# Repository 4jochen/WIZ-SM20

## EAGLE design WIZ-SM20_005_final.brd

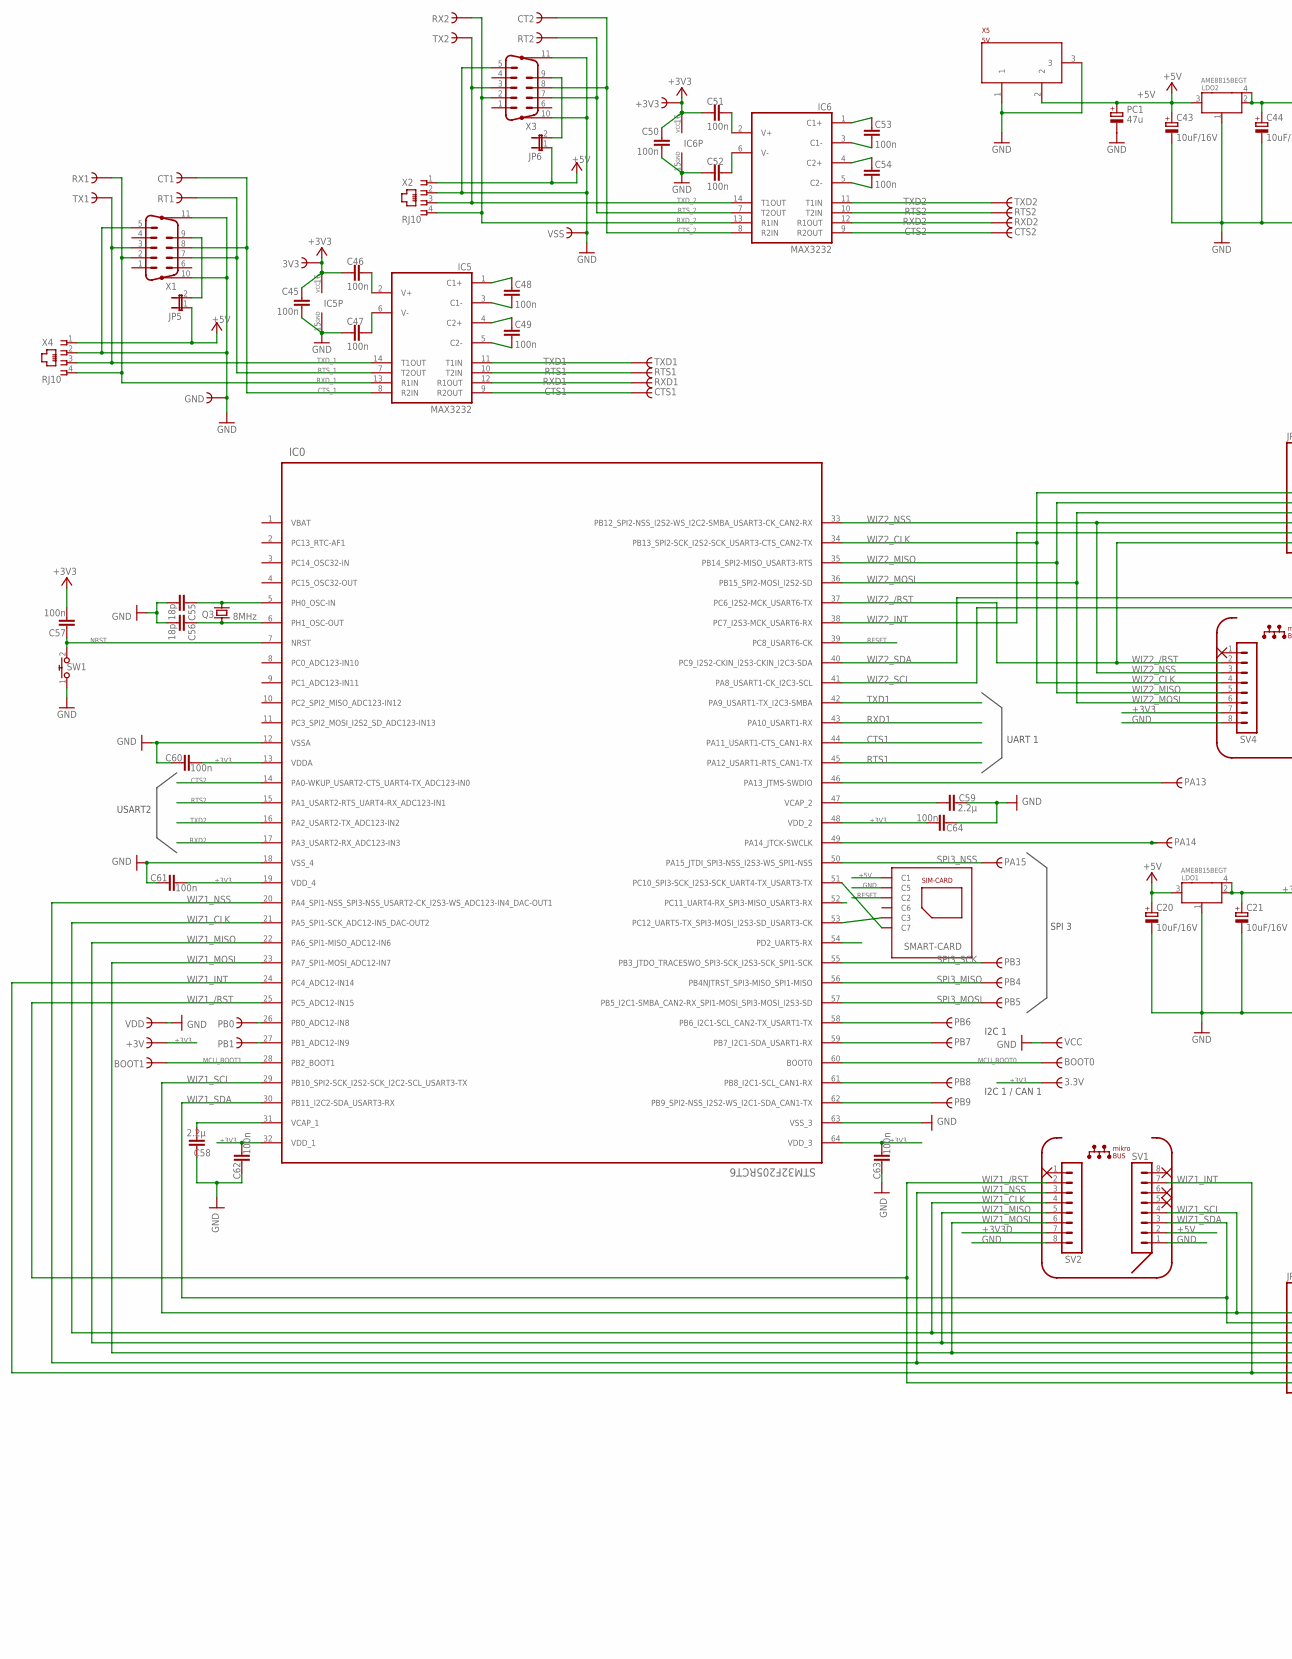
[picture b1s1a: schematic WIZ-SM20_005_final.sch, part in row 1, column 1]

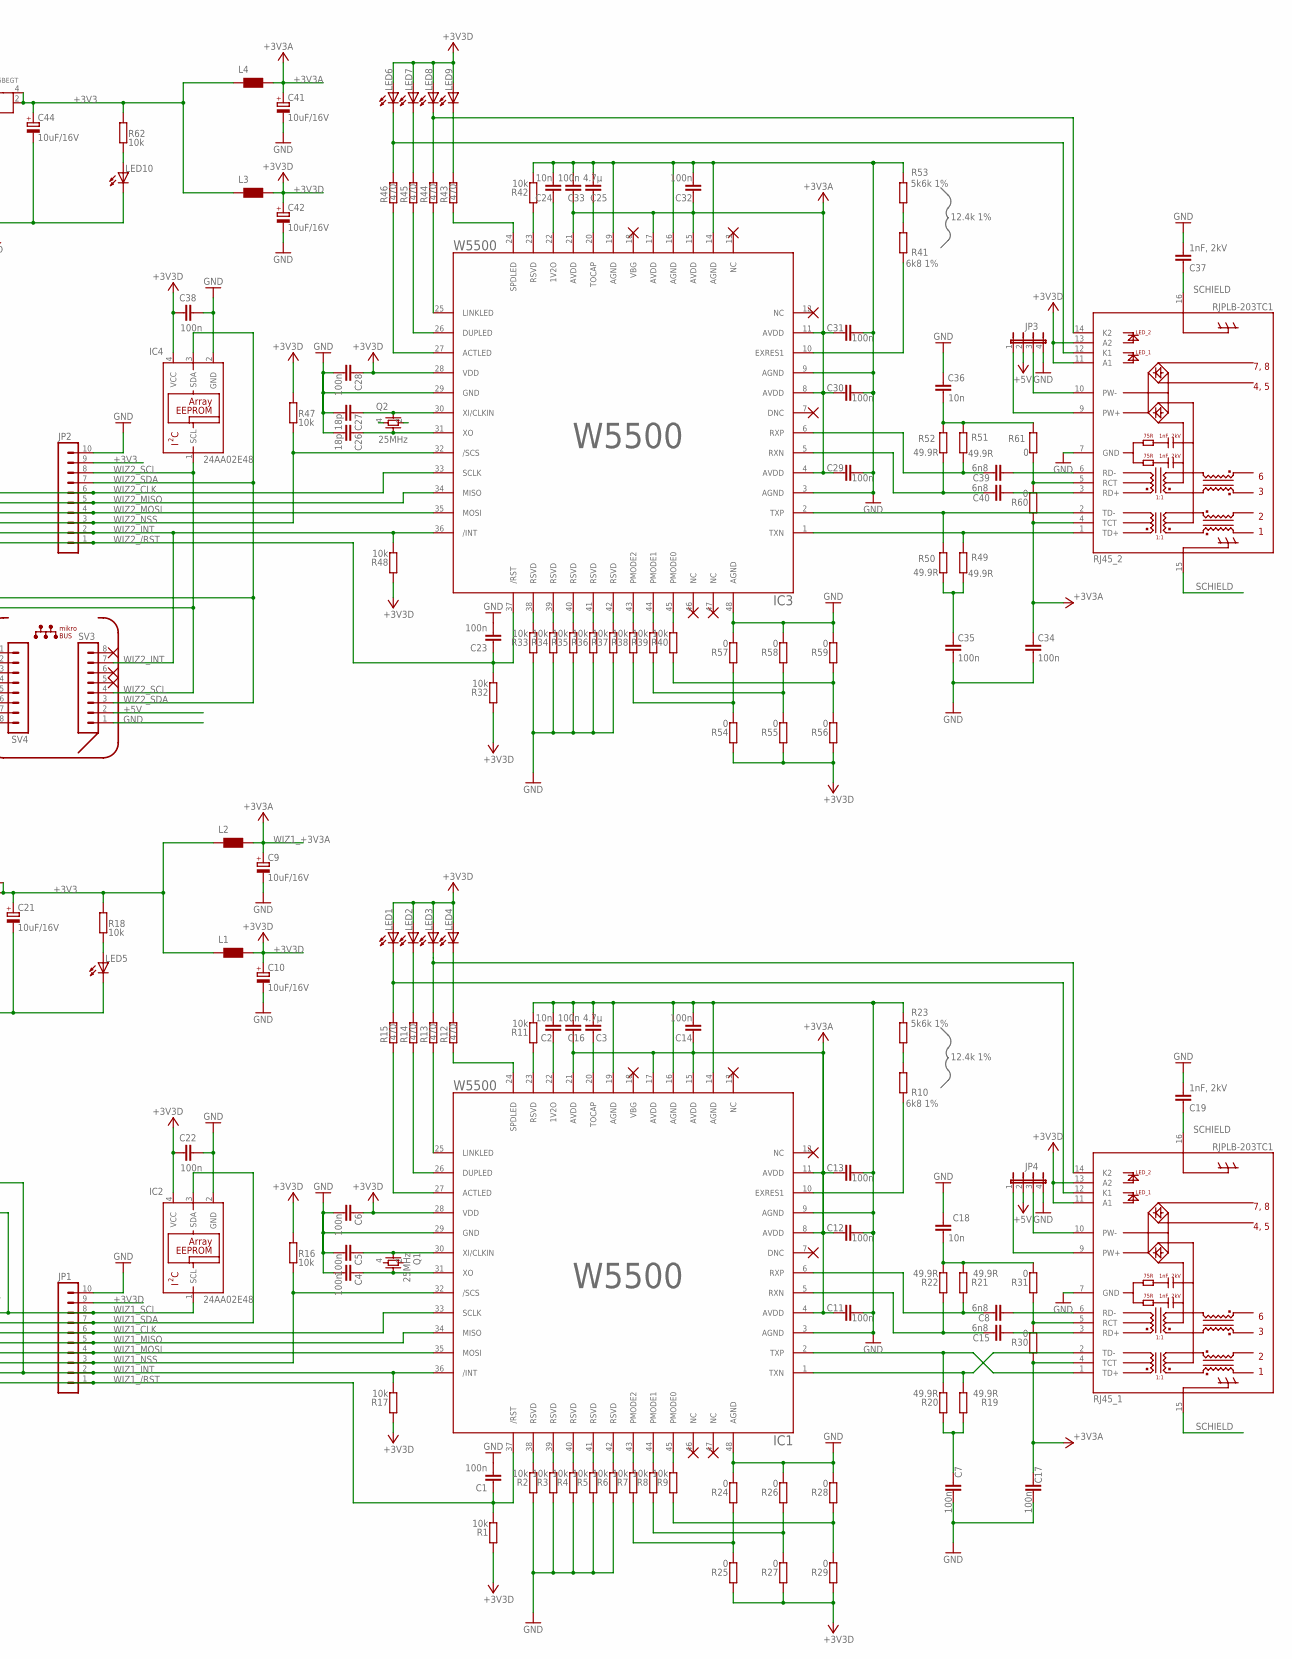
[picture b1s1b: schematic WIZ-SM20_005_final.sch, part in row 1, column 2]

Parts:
3.3V, 3V3: HALFHOLE
+3V, +3V3: HALFHOLE
BOOT0, BOOT1: HALFHOLE
C1, C23: 100n; C0603K
C2, C18, C24, C36: 10n; C0402K
C3, C25: 4.7µ; C0603K
C4, C5, C6, C7, C11, C12, C13, C14, C16, C17, C22, C28, C29, C30, C31, C32, C33, C34, C35, C38, C45, C46, C47, C48, C49, C50, C51, C52, C53, C54, C57, C60, C61, C62, C63, C64: 100n; C0402K
C8, C15, C39, C40: 6n8; C0402K
C9, C10, C20, C21, C41, C42, C43, C44: 10uF/16V; A/3216-18R
C19, C37: 1nF, 2kV; C3216
C26, C27, C55, C56: 18p; C0402K
C58, C59: 2.2µ; C0603K
CT1, CT2: HALFHOLE
CTS1, CTS2: HALFHOLE
GND: HALFHOLE
IC0: STM32F205RCT6; QFP50P1200X1200X160-64N
IC1, IC3: W5500; LQFP48
IC2, IC4: 24AA02E48; SOT23-5L
IC5, IC6: MAX3232; TSSOP16-L
JP1, JP2: @ Tessel; MA10-1
JP3, JP4: JP4E; JP4
JP5, JP6: JP1E; JP1
L1, L2, L3, L4: WE-CBF_0603; 0603
LDO1, LDO2: AME8815BEGT; SOT223
LED1, LED2, LED3, LED4, LED5, LED6, LED7, LED8, LED9, LED10: LEDCHIPLED_0603; CHIPLED_0603
PA13, PA14, PA15: HALFHOLE
PB0, PB1, PB3, PB4, PB5, PB6, PB7, PB8, PB9: HALFHOLE
PC1: 47u; A/3216-18R
Q1, Q2: 25MHz; SMD02502-4
Q3: 8MHz; ABM7
R1, R2, R3, R4, R5, R6, R7, R8, R9, R11, R16, R17, R18, R32, R33, R34, R35, R36, R37, R38, R39, R40, R42, R47, R48, R62: 10k; R0402
R10, R41: 6k8 1%; R0402
R12, R13, R14, R15, R43, R44, R45, R46: 470; R0402
R19, R20, R21, R22, R49, R50, R51, R52: 49.9R; R0402
R23, R53: 5k6k 1%; R0402
R24, R25, R26, R27, R28, R29, R30, R31, R54, R55, R56, R57, R58, R59, R60, R61: 0; R0402
RJ45_1, RJ45_2: RJPLB-203TC1; RJPLB-203
RT1, RT2: HALFHOLE
RTS1, RTS2: HALFHOLE
RX1, RX2: HALFHOLE
RXD1, RXD2: HALFHOLE
SMART-CARD: 7111S2015X02LF
SV1, SV2, SV3, SV4: MA08-1
SW1: Reset; 1302
TX1, TX2: HALFHOLE
TXD1, TXD2: HALFHOLE
VCC: HALFHOLE
VDD: HALFHOLE
VSS: HALFHOLE
X1, X3: M09HPSLIM_SMD; NORCOMP_SMD
X2, X4: RJ10; 520249-2
X5: 5V; POWERSUPPLY_DC-21MM

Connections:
+3V3: 3.3V.P$1, 3V3.P$1, +3V.P$1, +3V3.P$1, C21.+, C44.+, C45.2, C46.1, C50.2, C51.1, C60.2, C61.2, C62.2, C63.2, C64.2, IC0.13 (VDDA), IC0.19 (VDD_4), IC0.32 (VDD_1), IC0.48 (VDD_2), IC0.64 (VDD_3), IC5.16 (VCC), IC6.16 (VCC), JP2.9, L1.2, L2.2, L3.2, L4.2, LDO1.2, LDO1.4, LDO2.2, LDO2.4, R18.2, R62.2, SV4.7
+3V3A: C29.1, C30.1, C31.1, C32.1, C33.1, C34.1, C41.+, IC3.4 (AVDD), IC3.8 (AVDD), IC3.11 (AVDD), IC3.15 (AVDD), IC3.17 (AVDD), IC3.21 (AVDD), L4.1, R60.2, RJ45_2.4 (TCT)
+3V3D: C6.1, C10.+, C22.1, C28.1, C38.1, C42.+, IC1.28 (VDD), IC2.4 (VCC), IC3.28 (VDD), IC4.4 (VCC), JP1.9, L1.1, L3.1, LED1.A, LED2.A, LED3.A, LED4.A, LED6.A, LED7.A, LED8.A, LED9.A, R1.2, R16.2, R17.2, R25.2, R27.2, R29.2, R32.2, R47.2, R48.2, R54.2, R55.2, R56.2, RJ45_1.11 (A1), RJ45_1.13 (A2), RJ45_2.11 (A1), RJ45_2.13 (A2), SV2.7
+5V: C20.+, C43.+, JP3.2, JP4.2, JP5.1, JP6.1, LDO1.3, LDO2.3, PC1.+, SMART-CARD.C1, SV1.2, SV3.2, X2.1, X4.1, X5.2
ACTLED: IC1.27 (ACTLED), R15.1
ACTLED1: IC3.27 (ACTLED), R46.1
CTS1: CTS1.P$1, IC0.44 (PA11_USART1-CTS_CAN1-RX), IC5.9 (R2OUT)
CTS2: CTS2.P$1, IC0.14 (PA0-WKUP_USART2-CTS_UART4-TX_ADC123-IN0), IC6.9 (R2OUT)
CTS_1: CT1.P$1, IC5.8 (R2IN), X1.8
CTS_2: CT2.P$1, IC6.8 (R2IN), X3.8
GND: C1.2, C2.2, C3.2, C4.2, C5.2, C6.2, C7.2, C9.-, C10.-, C11.2, C12.2, C13.2, C14.2, C16.2, C17.2, C18.2, C19.2, C20.-, C21.-, C22.2, C23.2, C24.2, C25.2, C26.2, C27.2, C28.2, C29.2, C30.2, C31.2, C32.2, C33.2, C34.2, C35.2, C36.2, C37.2, C38.2, C41.-, C42.-, C43.-, C44.-, C45.1, C47.1, C50.1, C52.1, C55.2, C56.2, C58.1, C59.1, C60.1, C61.1, C62.1, C63.1, C64.1, GND.P$1, IC0.12 (VSSA), IC0.18 (VSS_4), IC0.63 (VSS_3), IC1.3 (AGND), IC1.9 (AGND), IC1.14 (AGND), IC1.16 (AGND), IC1.19 (AGND), IC1.29 (GND), IC1.48 (AGND), IC2.2 (GND), IC3.3 (AGND), IC3.9 (AGND), IC3.14 (AGND), IC3.16 (AGND), IC3.19 (AGND), IC3.29 (GND), IC3.48 (AGND), IC4.2 (GND), IC5.15 (GND), IC6.15 (GND), JP1.10, JP2.10, JP3.4, JP4.4, LDO1.1, LDO2.1, LED5.C, LED10.C, PC1.-, Q2.2 (PD1), Q2.4 (PD2), R2.2, R3.2, R4.2, R5.2, R6.2, R11.1, R23.1, R24.1, R26.1, R28.1, R33.2, R34.2, R35.2, R36.2, R37.2, R42.1, R53.1, R57.1, R58.1, R59.1, RJ45_1.7 (GND), RJ45_2.7 (GND), SMART-CARD.C5, SV1.1, SV2.8, SV3.1, SV4.8, SW1.1, VCC.P$1, VDD.P$1, VSS.P$1, X1.5, X1.10 (G1), X1.11 (G2), X2.2, X3.5, X3.10 (G1), X3.11 (G2), X4.2, X5.1, X5.3
MCU_BOOT0: BOOT0.P$1, IC0.60 (BOOT0)
MCU_BOOT1: BOOT1.P$1, IC0.28 (PB2_BOOT1)
unnamed: C8.1, RJ45_1.6 (RD-)
unnamed: C15.1, RJ45_1.3 (RD+)
unnamed: IC3.38 (RSVD), R33.1
unnamed: IC1.25 (LINKLED), R13.1
unnamed: R10.1, R23.2
unnamed: IC3.39 (RSVD), R34.1
unnamed: IC3.40 (RSVD), R35.1
unnamed: IC3.41 (RSVD), R36.1
unnamed: IC1.23 (RSVD), R11.2
unnamed: IC1.38 (RSVD), R2.1
unnamed: IC1.39 (RSVD), R3.1
unnamed: IC1.40 (RSVD), R4.1
unnamed: IC1.41 (RSVD), R5.1
unnamed: IC1.42 (RSVD), R6.1
unnamed: IC1.43 (PMODE2), R7.1
unnamed: IC1.44 (PMODE1), R8.1
unnamed: IC1.45 (PMODE0), R9.1
unnamed: R9.2, R28.2, R29.1
unnamed: R8.2, R26.2, R27.1
unnamed: R7.2, R24.2, R25.1
unnamed: IC3.42 (RSVD), R37.1
unnamed: IC1.10 (EXRES1), R10.2
unnamed: C2.1, IC1.22 (1V2O)
unnamed: C3.1, IC1.20 (TOCAP)
unnamed: IC1.24 (SPDLED), R12.1
unnamed: IC1.26 (DUPLED), R14.1
unnamed: IC3.43 (PMODE2), R38.1
unnamed: LED4.C, R12.2
unnamed: LED1.C, R15.2, RJ45_1.12 (K1)
unnamed: LED2.C, R14.2
unnamed: LED3.C, R13.2, RJ45_1.14 (K2)
unnamed: C4.1, IC1.31 (XO), Q1.3 (2)
unnamed: C5.1, IC1.30 (XI/CLKIN), Q1.1
unnamed: LED5.A, R18.1
unnamed: C7.1, R19.2, R20.2
unnamed: C18.1, R21.1, R22.1, R31.1
unnamed: IC3.44 (PMODE1), R39.1
unnamed: IC3.45 (PMODE0), R40.1
unnamed: IC3.10 (EXRES1), R41.2
unnamed: IC3.23 (RSVD), R42.2
unnamed: C24.1, IC3.22 (1V2O)
unnamed: C25.1, IC3.20 (TOCAP)
unnamed: IC3.24 (SPDLED), R43.1
unnamed: IC3.26 (DUPLED), R45.1
unnamed: LED9.C, R43.2
unnamed: LED6.C, R46.2, RJ45_2.12 (K1)
unnamed: LED7.C, R45.2
unnamed: LED8.C, R44.2, RJ45_2.14 (K2)
unnamed: C26.1, IC3.31 (XO), Q2.3 (2)
unnamed: C27.1, IC3.30 (XI/CLKIN), Q2.1
unnamed: C35.1, R49.2, R50.2
unnamed: C36.1, R51.1, R52.1, R61.1
unnamed: IC3.25 (LINKLED), R44.1
unnamed: R41.1, R53.2
unnamed: R38.2, R54.1, R57.2
unnamed: R39.2, R55.1, R58.2
unnamed: R40.2, R56.1, R59.2
unnamed: IC0.46 (PA13_JTMS-SWDIO), PA13.P$1
unnamed: IC0.49 (PA14_JTCK-SWCLK), PA14.P$1
unnamed: LED10.A, R62.1
unnamed: IC0.51 (PC10_SPI3-SCK_I2S3-SCK_UART4-TX_USART3-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), SMART-CARD.C7
unnamed: C55.1, IC0.5 (PH0_OSC-IN), Q3.1
unnamed: C56.1, IC0.6 (PH1_OSC-OUT), Q3.2
unnamed: IC0.26 (PB0_ADC12-IN8), PB0.P$1
unnamed: IC0.27 (PB1_ADC12-IN9), PB1.P$1
unnamed: IC0.53 (PC12_UART5-TX_SPI3-MOSI_I2S3-SD_USART3-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), SMART-CARD.C3
unnamed: IC0.61 (PB8_I2C1-SCL_CAN1-RX), PB8.P$1
unnamed: IC0.62 (PB9_SPI2-NSS_I2S2-WS_I2C1-SDA_CAN1-TX), PB9.P$1
unnamed: IC0.58 (PB6_I2C1-SCL_CAN2-TX_USART1-TX), PB6.P$1
unnamed: C53.2, IC6.1 (C1+)
unnamed: C48.2, IC5.1 (C1+)
unnamed: C48.1, IC5.3 (C1-)
unnamed: C49.2, IC5.4 (C2+)
unnamed: C49.1, IC5.5 (C2-)
unnamed: C46.2, IC5.2 (V+)
unnamed: C47.2, IC5.6 (V-)
unnamed: C53.1, IC6.3 (C1-)
unnamed: C54.2, IC6.4 (C2+)
unnamed: C54.1, IC6.5 (C2-)
unnamed: C51.2, IC6.2 (V+)
unnamed: JP5.2, X1.9
unnamed: C52.2, IC6.6 (V-)
unnamed: IC0.59 (PB7_I2C1-SDA_USART1-RX), PB7.P$1
unnamed: JP6.2, X3.9
unnamed: C58.2, IC0.31 (VCAP_1)
unnamed: C59.2, IC0.47 (VCAP_2)
NRST: C57.1, IC0.7 (NRST), SW1.2
POE+: JP4.1, RJ45_1.9 (PW+)
POE+1: JP3.1, RJ45_2.9 (PW+)
POE-: JP4.3, RJ45_1.10 (PW-)
POE-1: JP3.3, RJ45_2.10 (PW-)
RCT: R30.1, R31.2, RJ45_1.5 (RCT)
RCT1: R60.1, R61.2, RJ45_2.5 (RCT)
RESET: IC0.39 (PC8_USART6-CK), SMART-CARD.C2
RTS1: IC0.45 (PA12_USART1-RTS_CAN1-TX), IC5.10 (T2IN), RTS1.P$1
RTS2: IC0.15 (PA1_USART2-RTS_UART4-RX_ADC123-IN1), IC6.10 (T2IN), RTS2.P$1
RTS_1: IC5.7 (T2OUT), RT1.P$1, X1.7
RTS_2: IC6.7 (T2OUT), RT2.P$1, X3.7
RX2_N: C39.1, RJ45_2.6 (RD-)
RX2_P: C40.1, RJ45_2.3 (RD+)
RXD1: IC0.43 (PA10_USART1-RX), IC5.12 (R1OUT), RXD1.P$1
RXD2: IC0.17 (PA3_USART2-RX_ADC123-IN3), IC6.12 (R1OUT), RXD2.P$1
RXD_1: IC5.13 (R1IN), RX1.P$1, X1.2, X4.4
RXD_2: IC6.13 (R1IN), RX2.P$1, X2.4, X3.2
RXN: C8.2, IC1.6 (RXP), R21.2
RXN1: C39.2, IC3.6 (RXP), R51.2
RXP: C15.2, IC1.5 (RXN), R22.2
RXP1: C40.2, IC3.5 (RXN), R52.2
SCHIELD: C19.1, C37.1, RJ45_1.15 (SCHIELD_1), RJ45_1.16 (SCHIELD_2), RJ45_2.15 (SCHIELD_1), RJ45_2.16 (SCHIELD_2)
SPI3_MISO: IC0.56 (PB4NJTRST_SPI3-MISO_SPI1-MISO), PB4.P$1
SPI3_MOSI: IC0.57 (PB5_I2C1-SMBA_CAN2-RX_SPI1-MOSI_SPI3-MO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), PB5.P$1
SPI3_NSS: IC0.50 (PA15_JTDI_SPI3-NSS_I2S3-WS_SPI1-NSS), PA15.P$1
SPI3_SCK: IC0.55 (PB3_JTDO_TRACESWO_SPI3-SCK_I2S3-SCK_SPI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), PB3.P$1
TX2_N: IC3.2 (TXP), R50.1, RJ45_2.2 (TD-)
TX2_P: IC3.1 (TXN), R49.1, RJ45_2.1 (TD+)
TXD1: IC0.42 (PA9_USART1-TX_I2C3-SMBA), IC5.11 (T1IN), TXD1.P$1
TXD2: IC0.16 (PA2_USART2-TX_ADC123-IN2), IC6.11 (T1IN), TXD2.P$1
TXD_1: IC5.14 (T1OUT), TX1.P$1, X1.3, X4.3
TXD_2: IC6.14 (T1OUT), TX2.P$1, X2.3, X3.3
TXN: IC1.2 (TXP), R20.1, RJ45_1.1 (TD+)
TXP: IC1.1 (TXN), R19.1, RJ45_1.2 (TD-)
VBAT: IC0.1 (VBAT)
VCC: C57.2
WIZ1_+3V3A: C9.+, C11.1, C12.1, C13.1, C14.1, C16.1, C17.1, IC1.4 (AVDD), IC1.8 (AVDD), IC1.11 (AVDD), IC1.15 (AVDD), IC1.17 (AVDD), IC1.21 (AVDD), L2.1, R30.2, RJ45_1.4 (TCT)
WIZ1_/RST: C1.1, IC0.25 (PC5_ADC12-IN15), IC1.37 (/RST), JP1.1, R1.1, SV2.2
WIZ1_CLK: IC0.21 (PA5_SPI1-SCK_ADC12-IN5_DAC-OUT2), IC1.33 (SCLK), JP1.6, SV2.4
WIZ1_INT: IC0.24 (PC4_ADC12-IN14), IC1.36 (/INT), JP1.2, R17.1, SV1.7
WIZ1_MISO: IC0.22 (PA6_SPI1-MISO_ADC12-IN6), IC1.34 (MISO), JP1.5, SV2.5
WIZ1_MOSI: IC0.23 (PA7_SPI1-MOSI_ADC12-IN7), IC1.35 (MOSI), JP1.4, SV2.6
WIZ1_NSS: IC0.20 (PA4_SPI1-NSS_SPI3-NSS_USART2-CK_I2S3-WS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), IC1.32 (/SCS), JP1.3, R16.1, SV2.3
WIZ1_SCL: IC0.29 (PB10_SPI2-SCK_I2S2-SCK_I2C2-SCL_USART3-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), IC2.1 (SCL), JP1.8, SV1.4
WIZ1_SDA: IC0.30 (PB11_I2C2-SDA_USART3-RX), IC2.3 (SDA), JP1.7, SV1.3
WIZ2_/RST: C23.1, IC0.37 (PC6_I2S2-MCK_USART6-TX), IC3.37 (/RST), JP2.1, R32.1, SV4.2
WIZ2_CLK: IC0.34 (PB13_SPI2-SCK_I2S2-SCK_USART3-CTS_CAN2-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), IC3.33 (SCLK), JP2.6, SV4.4
WIZ2_INT: IC0.38 (PC7_I2S3-MCK_USART6-RX), IC3.36 (/INT), JP2.2, R48.1, SV3.7
WIZ2_MISO: IC0.35 (PB14_SPI2-MISO_USART3-RTS), IC3.34 (MISO), JP2.5, SV4.5
WIZ2_MOSI: IC0.36 (PB15_SPI2-MOSI_I2S2-SD), IC3.35 (MOSI), JP2.4, SV4.6
WIZ2_NSS: IC0.33 (PB12_SPI2-NSS_I2S2-WS_I2C2-SMBA_USART3-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), IC3.32 (/SCS), JP2.3, R47.1, SV4.3
WIZ2_SCL: IC0.41 (PA8_USART1-CK_I2C3-SCL), IC4.1 (SCL), JP2.8, SV3.4
WIZ2_SDA: IC0.40 (PC9_I2S2-CKIN_I2S3-CKIN_I2C3-SDA), IC4.3 (SDA), JP2.7, SV3.3

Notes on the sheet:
W5500
12.4k 1%
mikro BUS
USART2
I2C 1 / CAN 1
I2C 1
UART 1
SPI 3

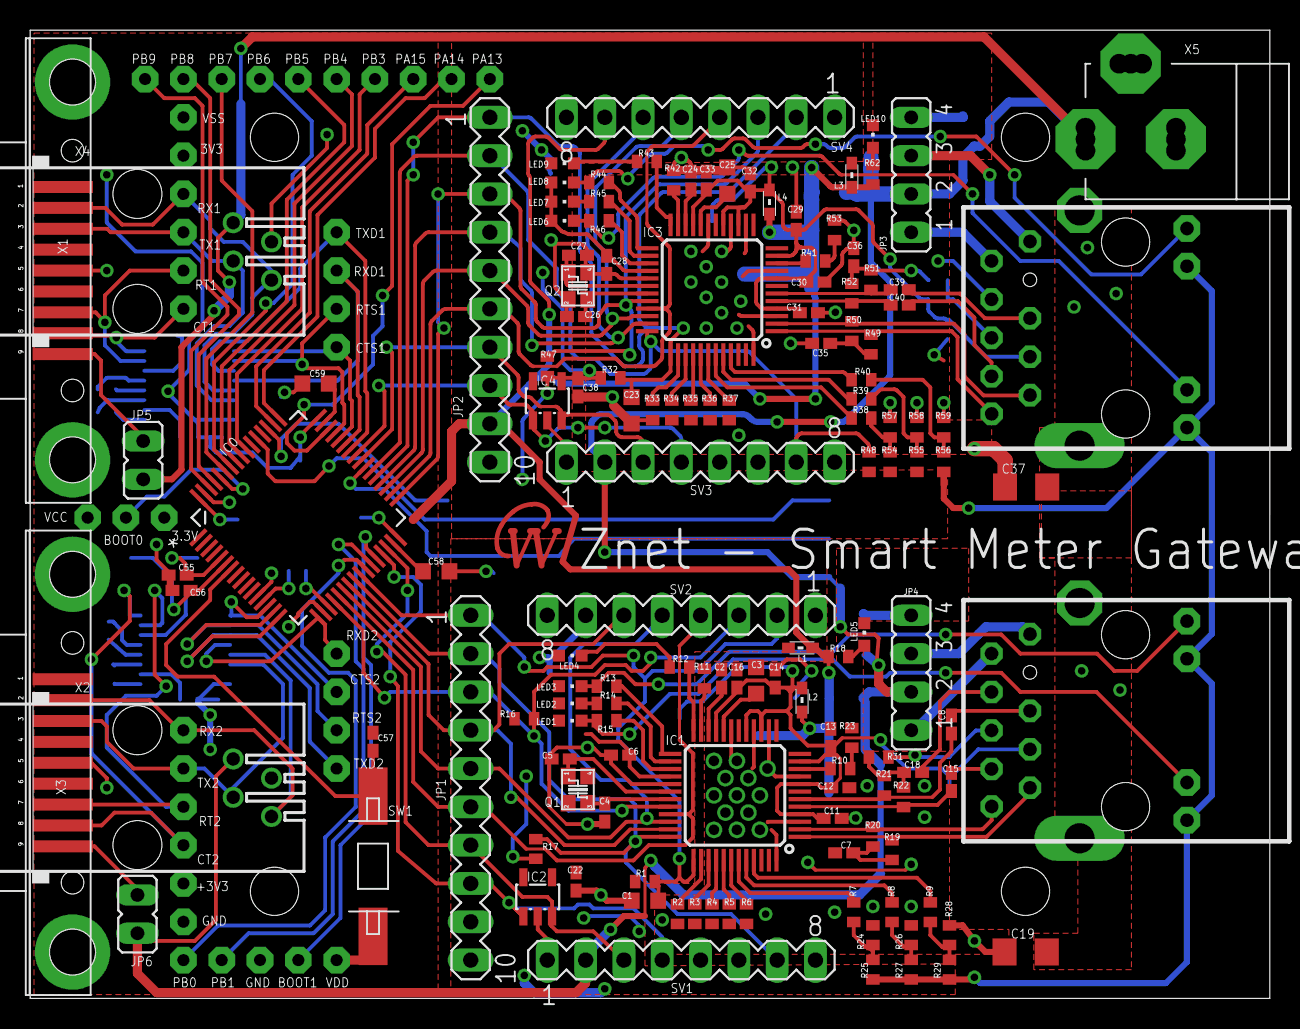
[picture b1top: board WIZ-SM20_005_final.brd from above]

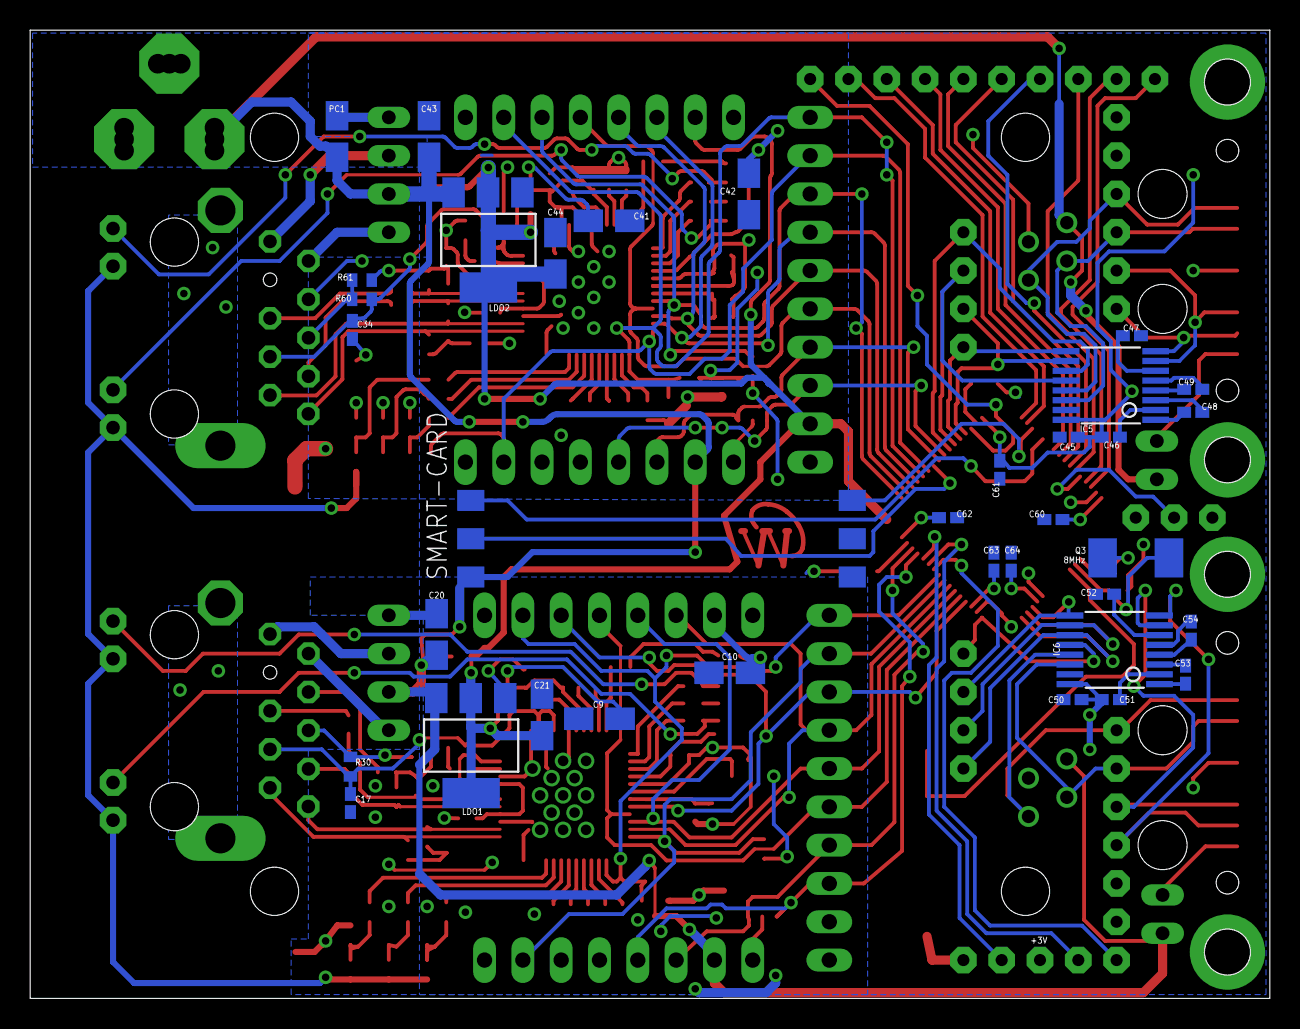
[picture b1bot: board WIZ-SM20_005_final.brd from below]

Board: 2 copper layers, 82.2 x 64.2 mm, 210 parts (36 on the bottom side), 151 nets.

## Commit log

2013-10-02 2x W5500 + STM32F205RCT6 MCU - first prototype
    Eagle schematic and brd file published
    created one PDF with Schematic and TOP + Bottom Layer pictures
2013-10-02 Drill Test PCB production feedback
    two pictures of the drill tests
2013-10-02 TOP and Bottom PCB phot. exposure
2013-10-02 STM32F205RCT6 pin function and use - XLS file added
2013-10-03 added pictures and create folder
2013-10-06 renamed pictures - added the printing
2013-10-08 PCB arrived, upload new pictures
2015-07-23 maybe xls was changed ?!?!, and pdf new

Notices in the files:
parts and their libraries:
wuerth-elektronik: Copyright: Würth Elektronik eiSos
